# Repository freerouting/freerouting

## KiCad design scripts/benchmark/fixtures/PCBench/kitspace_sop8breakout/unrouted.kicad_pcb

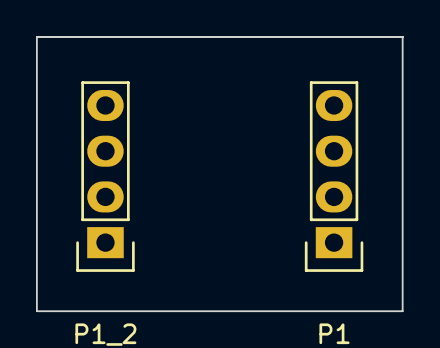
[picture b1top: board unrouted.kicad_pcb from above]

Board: 2 copper layers, 20.3 x 15.2 mm, 3 parts (1 on the bottom side), 8 nets, no tracks yet.

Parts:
IC1: MCP6002; SOP-8
P1, P1_2: CONN_01X04; Pin_Header_Straight_1x04

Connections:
unnamed: IC1.1, P1_2.1
unnamed: IC1.2, P1_2.2
unnamed: IC1.3, P1_2.3
unnamed: IC1.4, P1_2.4
unnamed: IC1.5, P1.4
unnamed: IC1.6, P1.3
unnamed: IC1.7, P1.2
unnamed: IC1.8, P1.1

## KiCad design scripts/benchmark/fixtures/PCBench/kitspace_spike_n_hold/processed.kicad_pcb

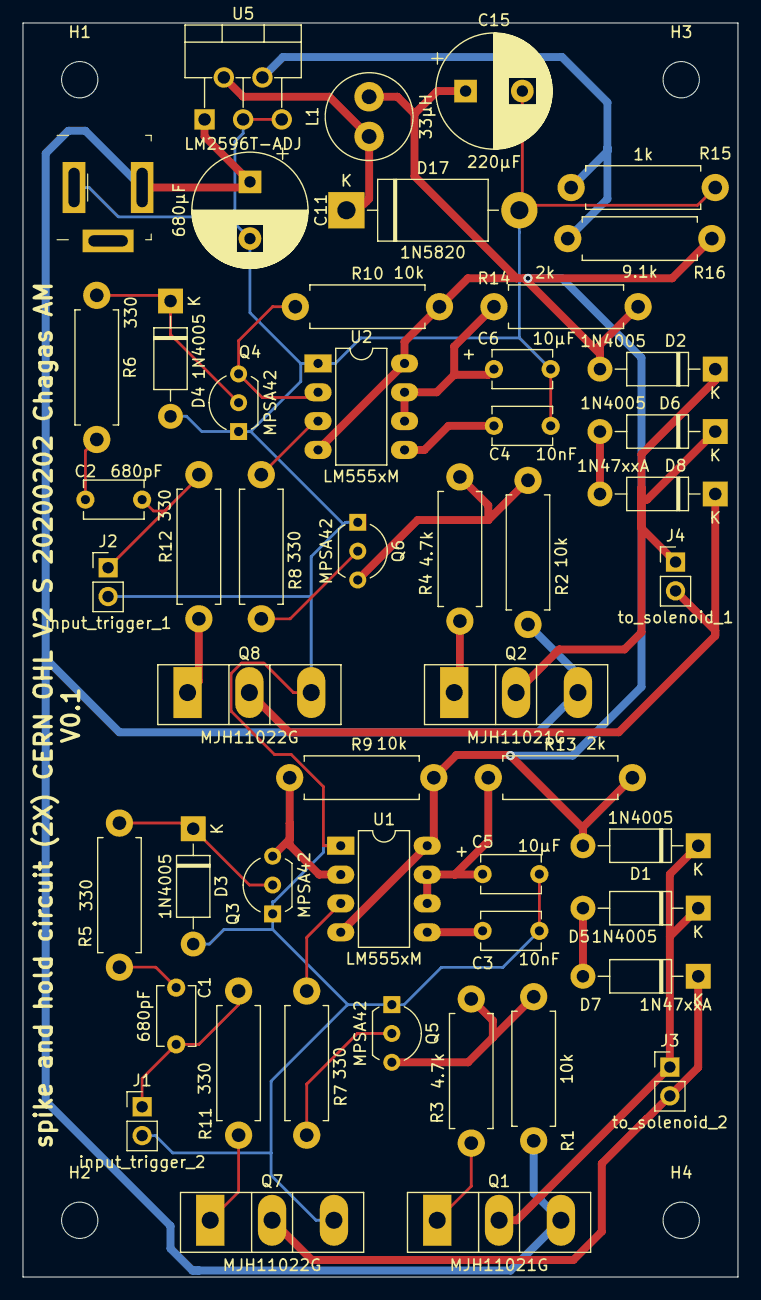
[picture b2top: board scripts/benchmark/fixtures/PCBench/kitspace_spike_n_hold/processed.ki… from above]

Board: 2 copper layers, 63.0 x 110.5 mm, 54 parts (0 on the bottom side), 33 nets.

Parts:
C1, C2: 680pF; C_Disc_D5.1mm_W3.2mm_P5.00mm
C3, C4: 10nF; C_Disc_D5.1mm_W3.2mm_P5.00mm
C5, C6: 10µF; C_Disc_D5.1mm_W3.2mm_P5.00mm
C11: 680µF; CP_Radial_D10.0mm_P5.00mm
C15: 220µF; CP_Radial_D10.0mm_P5.00mm
D1, D2, D3, D4, D5, D6: 1N4005; D_DO-41_SOD81_P10.16mm_Horizontal
D7, D8: 1N47xxA; D_DO-41_SOD81_P10.16mm_Horizontal
D17: 1N5820; D_DO-201AD_P15.24mm_Horizontal
H1, H2, H3, H4: MountingHole; MountingHole_3.2mm_M3
J1: input_trigger_2; PinHeader_1x02_P2.54mm_Vertical
J2: input_trigger_1; PinHeader_1x02_P2.54mm_Vertical
J3: to_solenoid_2; PinHeader_1x02_P2.54mm_Vertical
J4: to_solenoid_1; PinHeader_1x02_P2.54mm_Vertical
J9: Barrel_Jack_MountingPin; Barrel_Jack_5.5mmODx2.1mmID_PJ-202A
L1: 33µH; L_Radial_D7.5mm_P3.50mm_Fastron_07P
Q1, Q2: MJH11021G; TO-247-3_Vertical
Q3, Q4, Q5, Q6: MPSA42; TO-92L_Inline_Wide
Q7, Q8: MJH11022G; TO-247-3_Vertical
R1, R2, R9, R10: 10k; R_Axial_DIN0411_L9.9mm_D3.6mm_P12.70mm_Horizontal
R3, R4: 4.7k; R_Axial_DIN0411_L9.9mm_D3.6mm_P12.70mm_Horizontal
R5, R6, R7, R8, R11, R12: 330; R_Axial_DIN0411_L9.9mm_D3.6mm_P12.70mm_Horizontal
R13, R14: 2k; R_Axial_DIN0411_L9.9mm_D3.6mm_P12.70mm_Horizontal
R15: 1k; R_Axial_DIN0411_L9.9mm_D3.6mm_P12.70mm_Horizontal
R16: 9.1k; R_Axial_DIN0411_L9.9mm_D3.6mm_P12.70mm_Horizontal
U1, U2: LM555xM; DIP-8_W7.62mm_LongPads
U5: LM2596T-ADJ; TO-220-5_P3.4x3.7mm_StaggerOdd_Lead3.8mm_Vertical

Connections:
+12V: C15.1, D1.2, D2.2, L1.2, R9.2, R10.2, R13.2, R14.2, R16.2, U1.4, U1.8, U2.4, U2.8
+24V: C11.1, J9.1, Q1.3, Q2.3, R1.1, R2.1, U5.1
GND: C3.1, C4.1, C5.2, C6.2, C11.2, C15.2, D3.2, D4.2, D17.2, J1.2, J2.2, J9.2, Q3.1, Q4.1, Q5.1, Q6.1, Q7.3, Q8.3, R15.1, U1.1, U2.1, U5.3, U5.5
unnamed: C1.1, R5.2
unnamed: C2.1, R6.2
unnamed: C3.2, U1.5
unnamed: C4.2, U2.5
unnamed: C5.1, R13.1, U1.6, U1.7
unnamed: C6.1, R14.1, U2.6, U2.7
unnamed: D1.1, D5.1, J3.1, Q1.2
unnamed: D2.1, D6.1, J4.1, Q2.2
unnamed: D3.1, Q3.2, R5.1
unnamed: D4.1, Q4.2, R6.1
unnamed: D5.2, D7.2
unnamed: D6.2, D8.2
unnamed: D7.1, J3.2, Q7.2
unnamed: D8.1, J4.2, Q8.2
unnamed: D17.1, L1.1, U5.2
unnamed: Q1.1, R3.2
unnamed: Q2.1, R4.2
unnamed: Q3.3, R9.1, U1.2
unnamed: Q4.3, R10.1, U2.2
unnamed: Q5.2, R7.1
unnamed: Q5.3, R1.2, R3.1
unnamed: Q6.2, R8.1
unnamed: Q6.3, R2.2, R4.1
unnamed: Q7.1, R11.1
unnamed: Q8.1, R12.1
unnamed: R15.2, R16.1, U5.4
input_trigger1: C2.2, J2.1, R12.2
input_trigger2: C1.2, J1.1, R11.2
timed_trigger1: R8.2, U2.3
timed_trigger2: R7.2, U1.3

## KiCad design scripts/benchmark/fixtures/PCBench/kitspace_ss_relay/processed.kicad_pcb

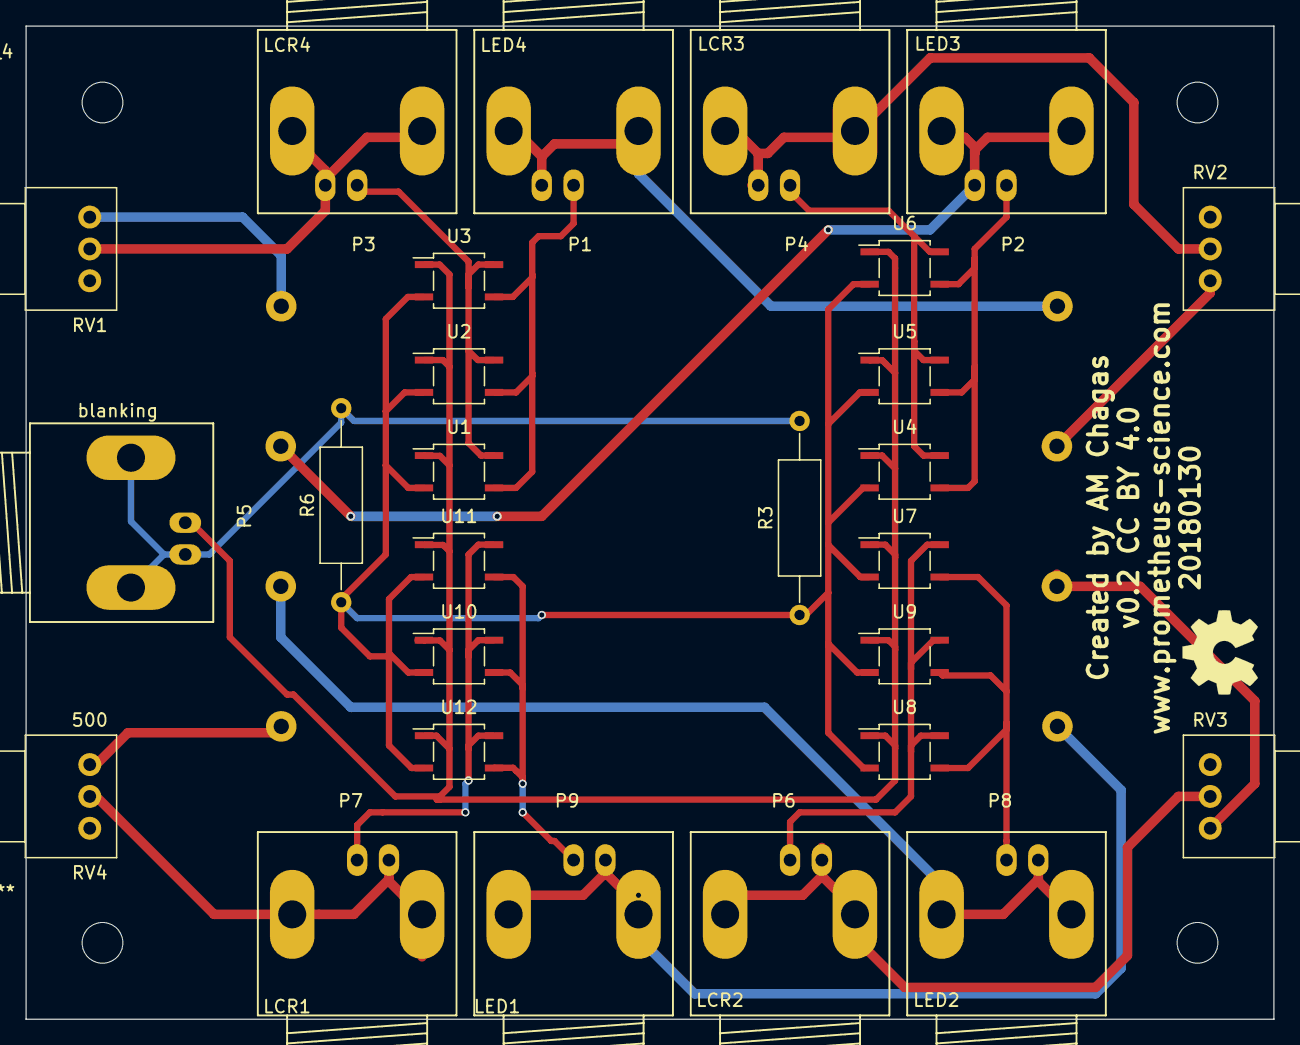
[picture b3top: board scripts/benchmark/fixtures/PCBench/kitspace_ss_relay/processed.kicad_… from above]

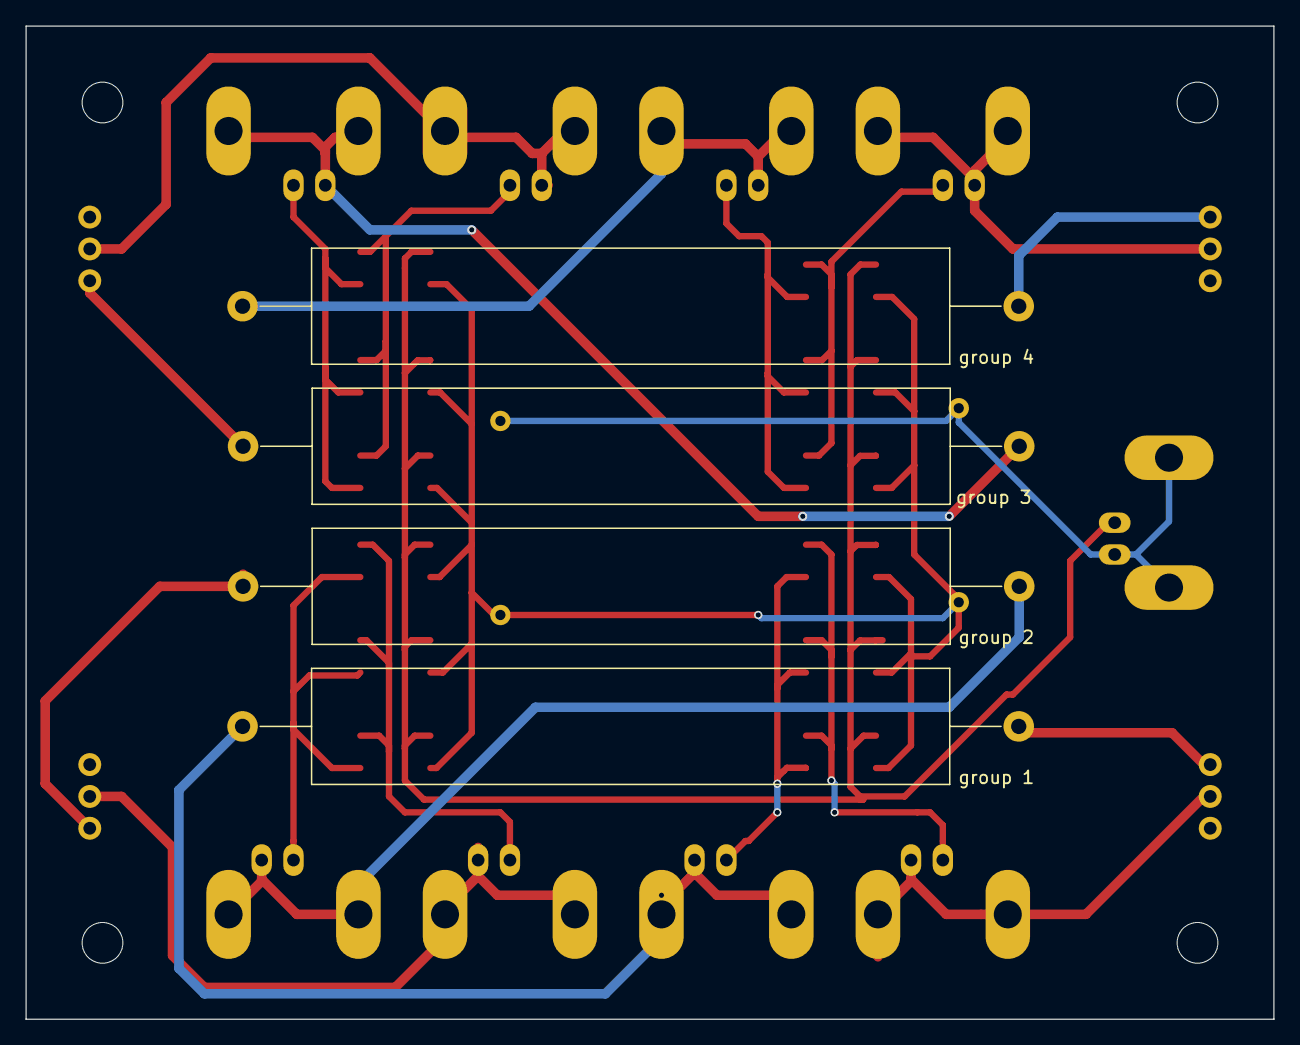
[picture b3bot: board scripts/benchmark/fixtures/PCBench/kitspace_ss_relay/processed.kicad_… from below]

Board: 2 copper layers, 98.0 x 78.0 mm, 31 parts (4 on the bottom side), 23 nets.

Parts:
P1: LED4; BNC_Socket_TYCO-AMP_LargePads
P2: LED3; BNC_Socket_TYCO-AMP_LargePads
P3: LCR4; BNC_Socket_TYCO-AMP_LargePads
P4: LCR3; BNC_Socket_TYCO-AMP_LargePads
P5: blanking; BNC_Socket_TYCO-AMP_LargePads
P6: LCR2; BNC_Socket_TYCO-AMP_LargePads
P7: LCR1; BNC_Socket_TYCO-AMP_LargePads
P8: LED2; BNC_Socket_TYCO-AMP_LargePads
P9: LED1; BNC_Socket_TYCO-AMP_LargePads
R3, R6: 270; R_Axial_DIN0309_L9.0mm_D3.2mm_P15.24mm_Horizontal
RV1, RV2, RV3, RV4: 500; Potentiometer_Alps_RK097_Single_Vertical
U1, U2, U3, U4, U5, U6, U7, U8, U9, U10, U11, U12: TLP291; SOP-4_3.8x4.1mm_Pitch2.54mm
group 1, group 2, group 3, group 4: 10; R_Axial_Power_L50.0mm_W9.0mm_P60.96mm

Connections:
GND: P5.2, R3.2, R6.2
unnamed: P1.1, U1.3, U2.3, U3.3
unnamed: P1.2, group 4.1
unnamed: P2.1, U4.3, U5.3, U6.3
unnamed: P2.2, group 3.1
unnamed: P3.1, U1.4, U2.4, U3.4
unnamed: P3.2, RV1.2
unnamed: P4.1, U4.4, U5.4, U6.4
unnamed: P4.2, RV2.2
unnamed: P5.1, U1.1, U2.1, U3.1, U4.1, U5.1, U6.1, U7.1, U8.1, U9.1, U10.1, U11.1, U12.1
unnamed: P6.1, U7.4, U8.4, U9.4
unnamed: P6.2, RV3.2
unnamed: P7.1, U10.4, U11.4, U12.4
unnamed: P7.2, RV4.2
unnamed: P8.1, U7.3, U8.3, U9.3
unnamed: P8.2, group 2.1
unnamed: P9.1, U10.3, U11.3, U12.3
unnamed: P9.2, group 1.1
unnamed: RV1.1, group 4.2
unnamed: RV2.1, group 3.2
unnamed: R3.1, R6.1, U1.2, U2.2, U3.2, U4.2, U5.2, U6.2, U7.2, U8.2, U9.2, U10.2, U11.2, U12.2
unnamed: RV3.1, group 2.2
unnamed: RV4.1, group 1.2

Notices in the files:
scripts/benchmark/fixtures/PCBench/kitspace_spike_n_hold/processed.kicad_pcb:
spike and hold circuit (2X) CERN OHL V2 S 20200202 Chagas AM
scripts/benchmark/fixtures/PCBench/kitspace_ss_relay/processed.kicad_pcb:
v0.2 CC BY 4.0
